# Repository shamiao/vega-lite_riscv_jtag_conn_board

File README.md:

# VEGA-Lite RISC-V JTAG Connection Board

> A board for connecting FreeLink headers to RISC-V JTAG port on VEGA-Lite development board.

## Notice

Work for VEGA-Lite only, doesn't work with VEGAboard. 

Designed with KiCad 5.1.4. 

## Contributing

Issues and pull requests are welcome, always. 

## License

Copyright (c) 2019 SHA Miao `<sha@miao.im>`

This project is licensed under [Solderpad Hardware License v. 0.51](http://www.apache.org/licenses/LICENSE-2.0) ([LICENSE](LICENSE)).

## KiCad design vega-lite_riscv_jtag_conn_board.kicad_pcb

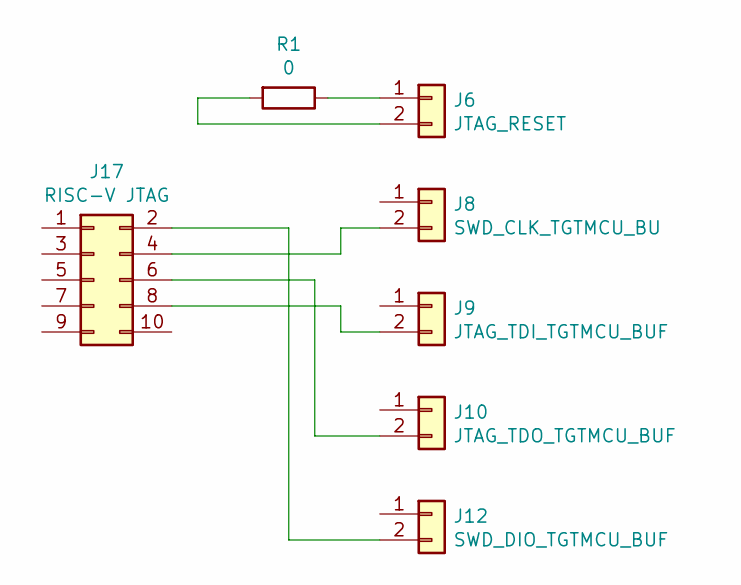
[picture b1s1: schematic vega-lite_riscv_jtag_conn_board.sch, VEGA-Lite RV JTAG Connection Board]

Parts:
J6: JTAG_RESET; PinHeader_1x02_P2.54mm_Vertical
J8: SWD_CLK_TGTMCU_BU; PinHeader_1x02_P2.54mm_Vertical
J9: JTAG_TDI_TGTMCU_BUF; PinHeader_1x02_P2.54mm_Vertical
J10: JTAG_TDO_TGTMCU_BUF; PinHeader_1x02_P2.54mm_Vertical
J12: SWD_DIO_TGTMCU_BUF; PinHeader_1x02_P2.54mm_Vertical
J17: RISC-V JTAG; PinHeader_2x05_P1.27mm_Vertical
R1: 0; R_0805_2012Metric_Pad1.15x1.40mm_HandSolder

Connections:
unnamed: J6.1, R1.1
unnamed: J6.2, R1.2
unnamed: J10.2, J17.6
unnamed: J12.2, J17.2
unnamed: J8.2, J17.4
unnamed: J9.2, J17.8

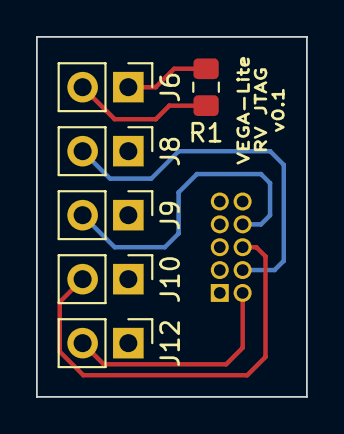
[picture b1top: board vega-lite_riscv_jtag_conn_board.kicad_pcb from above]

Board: 2 copper layers, 15.0 x 20.0 mm, 7 parts (1 on the bottom side), 6 nets.

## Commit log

2019-09-17 Add a rendered board image
